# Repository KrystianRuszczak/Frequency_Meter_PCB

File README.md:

# STM32 Frequency Meter PCB

A custom frequency meter built around the STM32G431KBT6 microcontroller, combining an analog input stage, a four-layer PCB, and an OLED display in a compact embedded system.

## Repository Contents

KiCad project files, schematics and PCB layout.

## Project Status

The project is under development. Measurement range, accuracy, and input limits will be documented after hardware assembly and validation.

## Key components

| Component | Part / type | Role |
| --- | --- | --- |
| Microcontroller | STM32G431KBT6 | Frequency measurement, USB communication, and display control. |
| Input amplifier | LMH6629MF/NOPB | Amplifies the filtered RF input signal. |
| Comparator | TLV3601DBVR | Converts the amplified analog signal into clock pulses. |
| Frequency divider | SN74LVC1G80 | Divides the comparator output frequency by two before counting by the microcontroller. |
| Voltage reference | REF2033 | Provides the 1.65 V reference for analog biasing and the comparator threshold. |
| Voltage regulator | AP2112K-3.3 | Provides the regulated 3.3 V supply. |
| Crystal | ABM3B-16.000MHZ-10-1-U-T | Provides the external 16 MHz clock reference for the microcontroller. |
| USB-C connector | USB4105-GF-A | Provides power and USB connectivity. |
| USB ESD protection | USBLC6-2SC6 | Protects the USB data lines against electrostatic discharge. |
| RF input connector | 50 Ω SMA | Connects the measured signal to the RF input filter. |
| Display | I2C OLED module | Displays measurement results. |

This list covers the main components. Refer to the KiCad schematic for passive components, supporting circuitry, and exact part variants.

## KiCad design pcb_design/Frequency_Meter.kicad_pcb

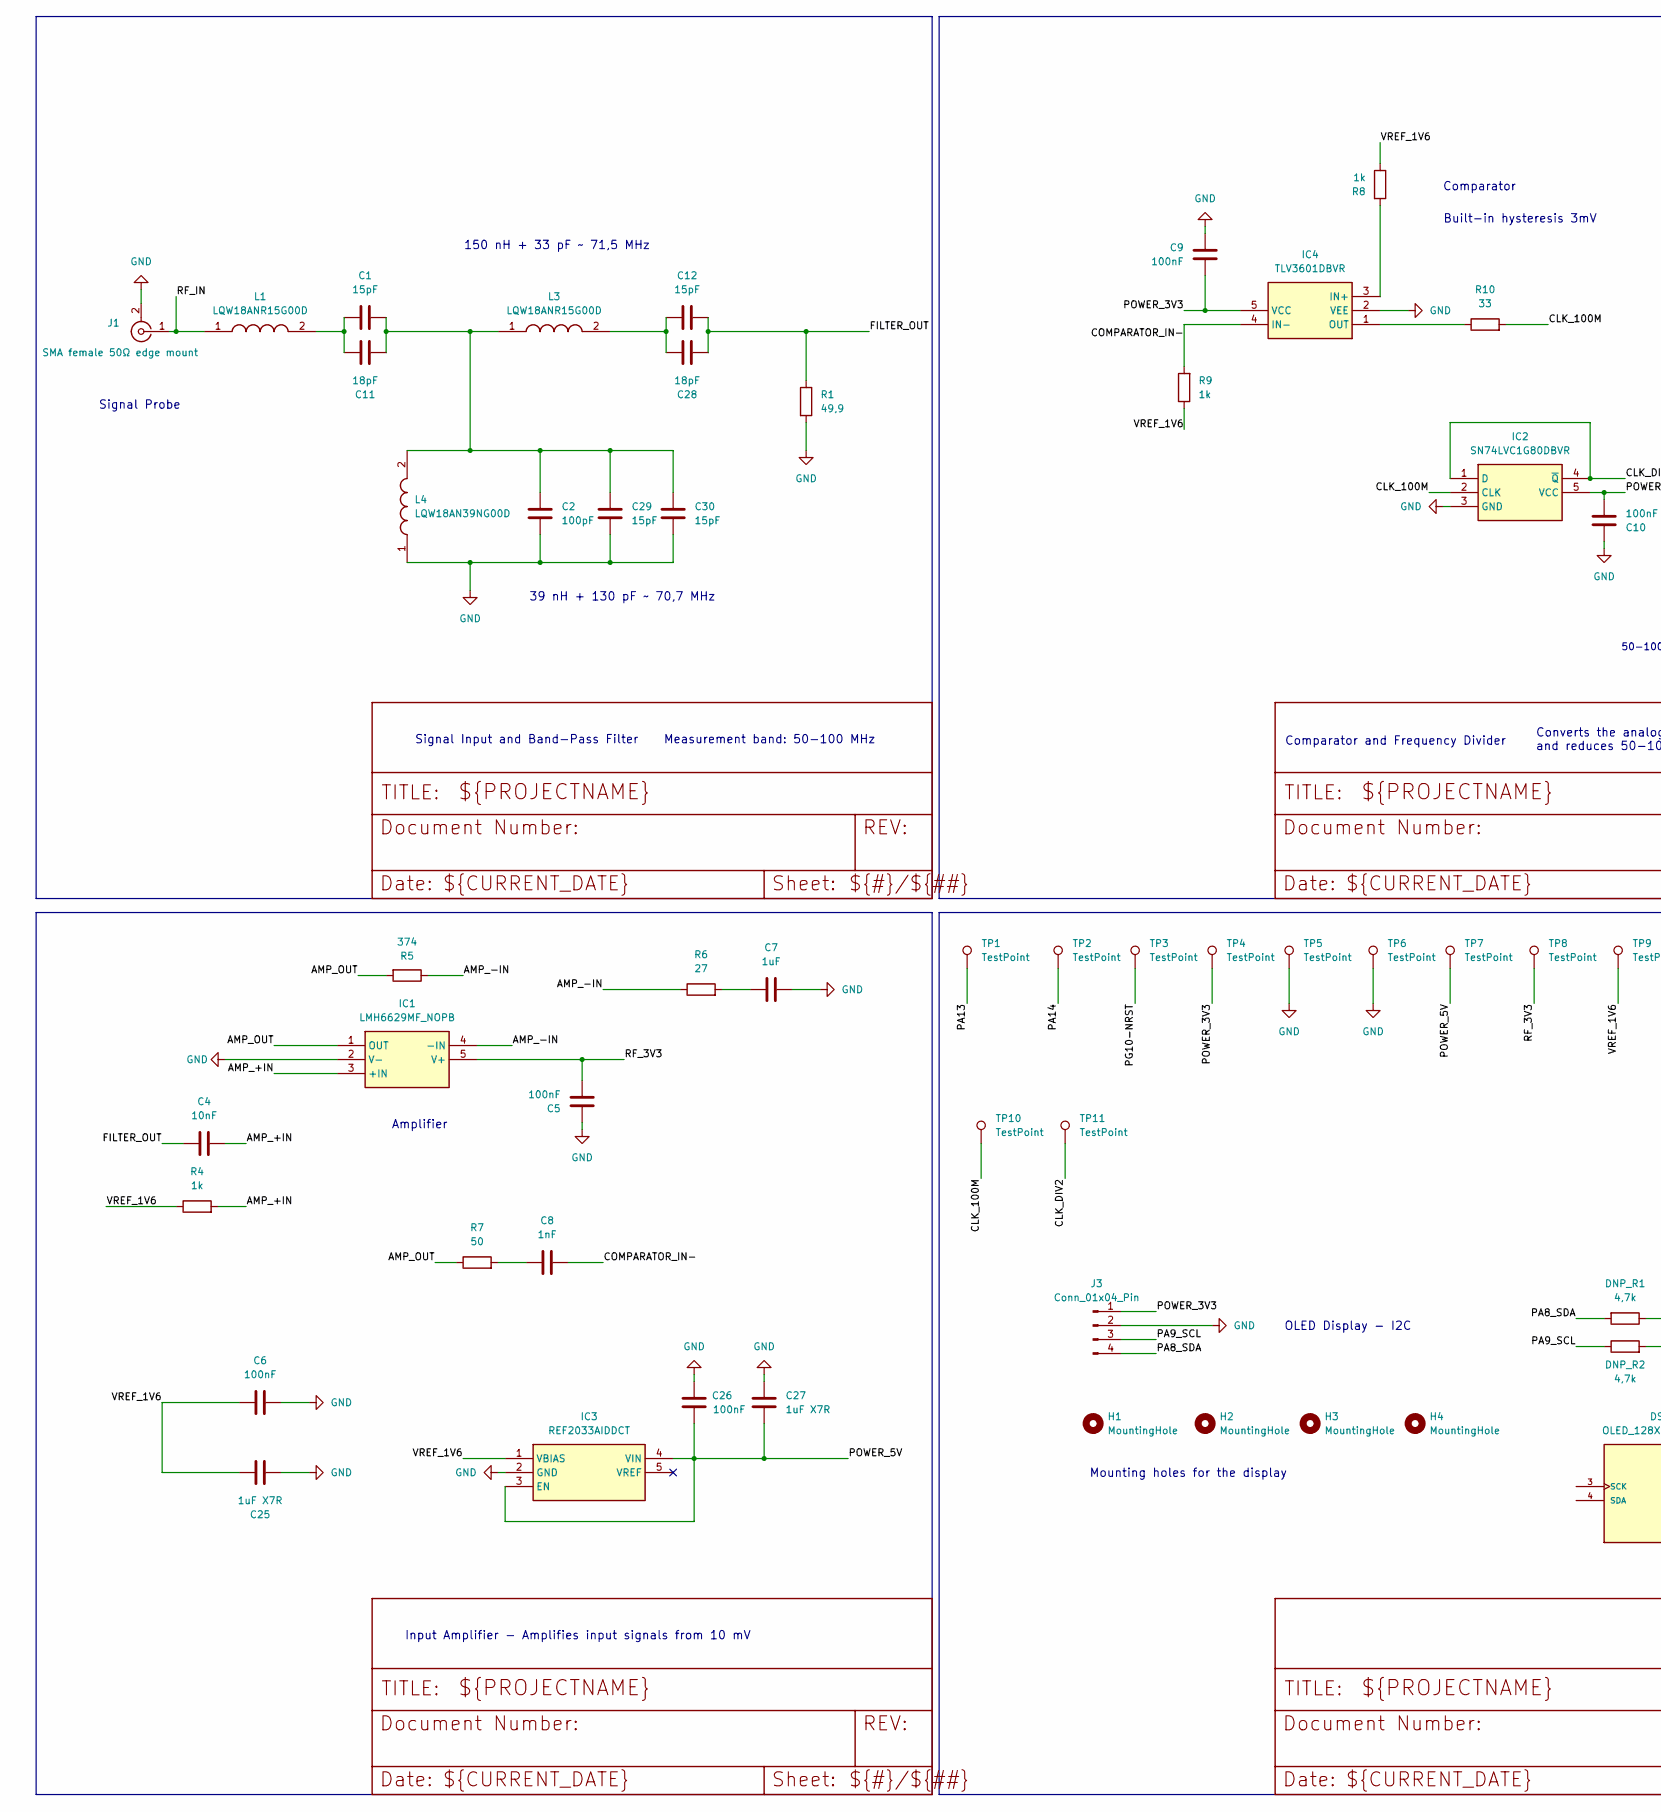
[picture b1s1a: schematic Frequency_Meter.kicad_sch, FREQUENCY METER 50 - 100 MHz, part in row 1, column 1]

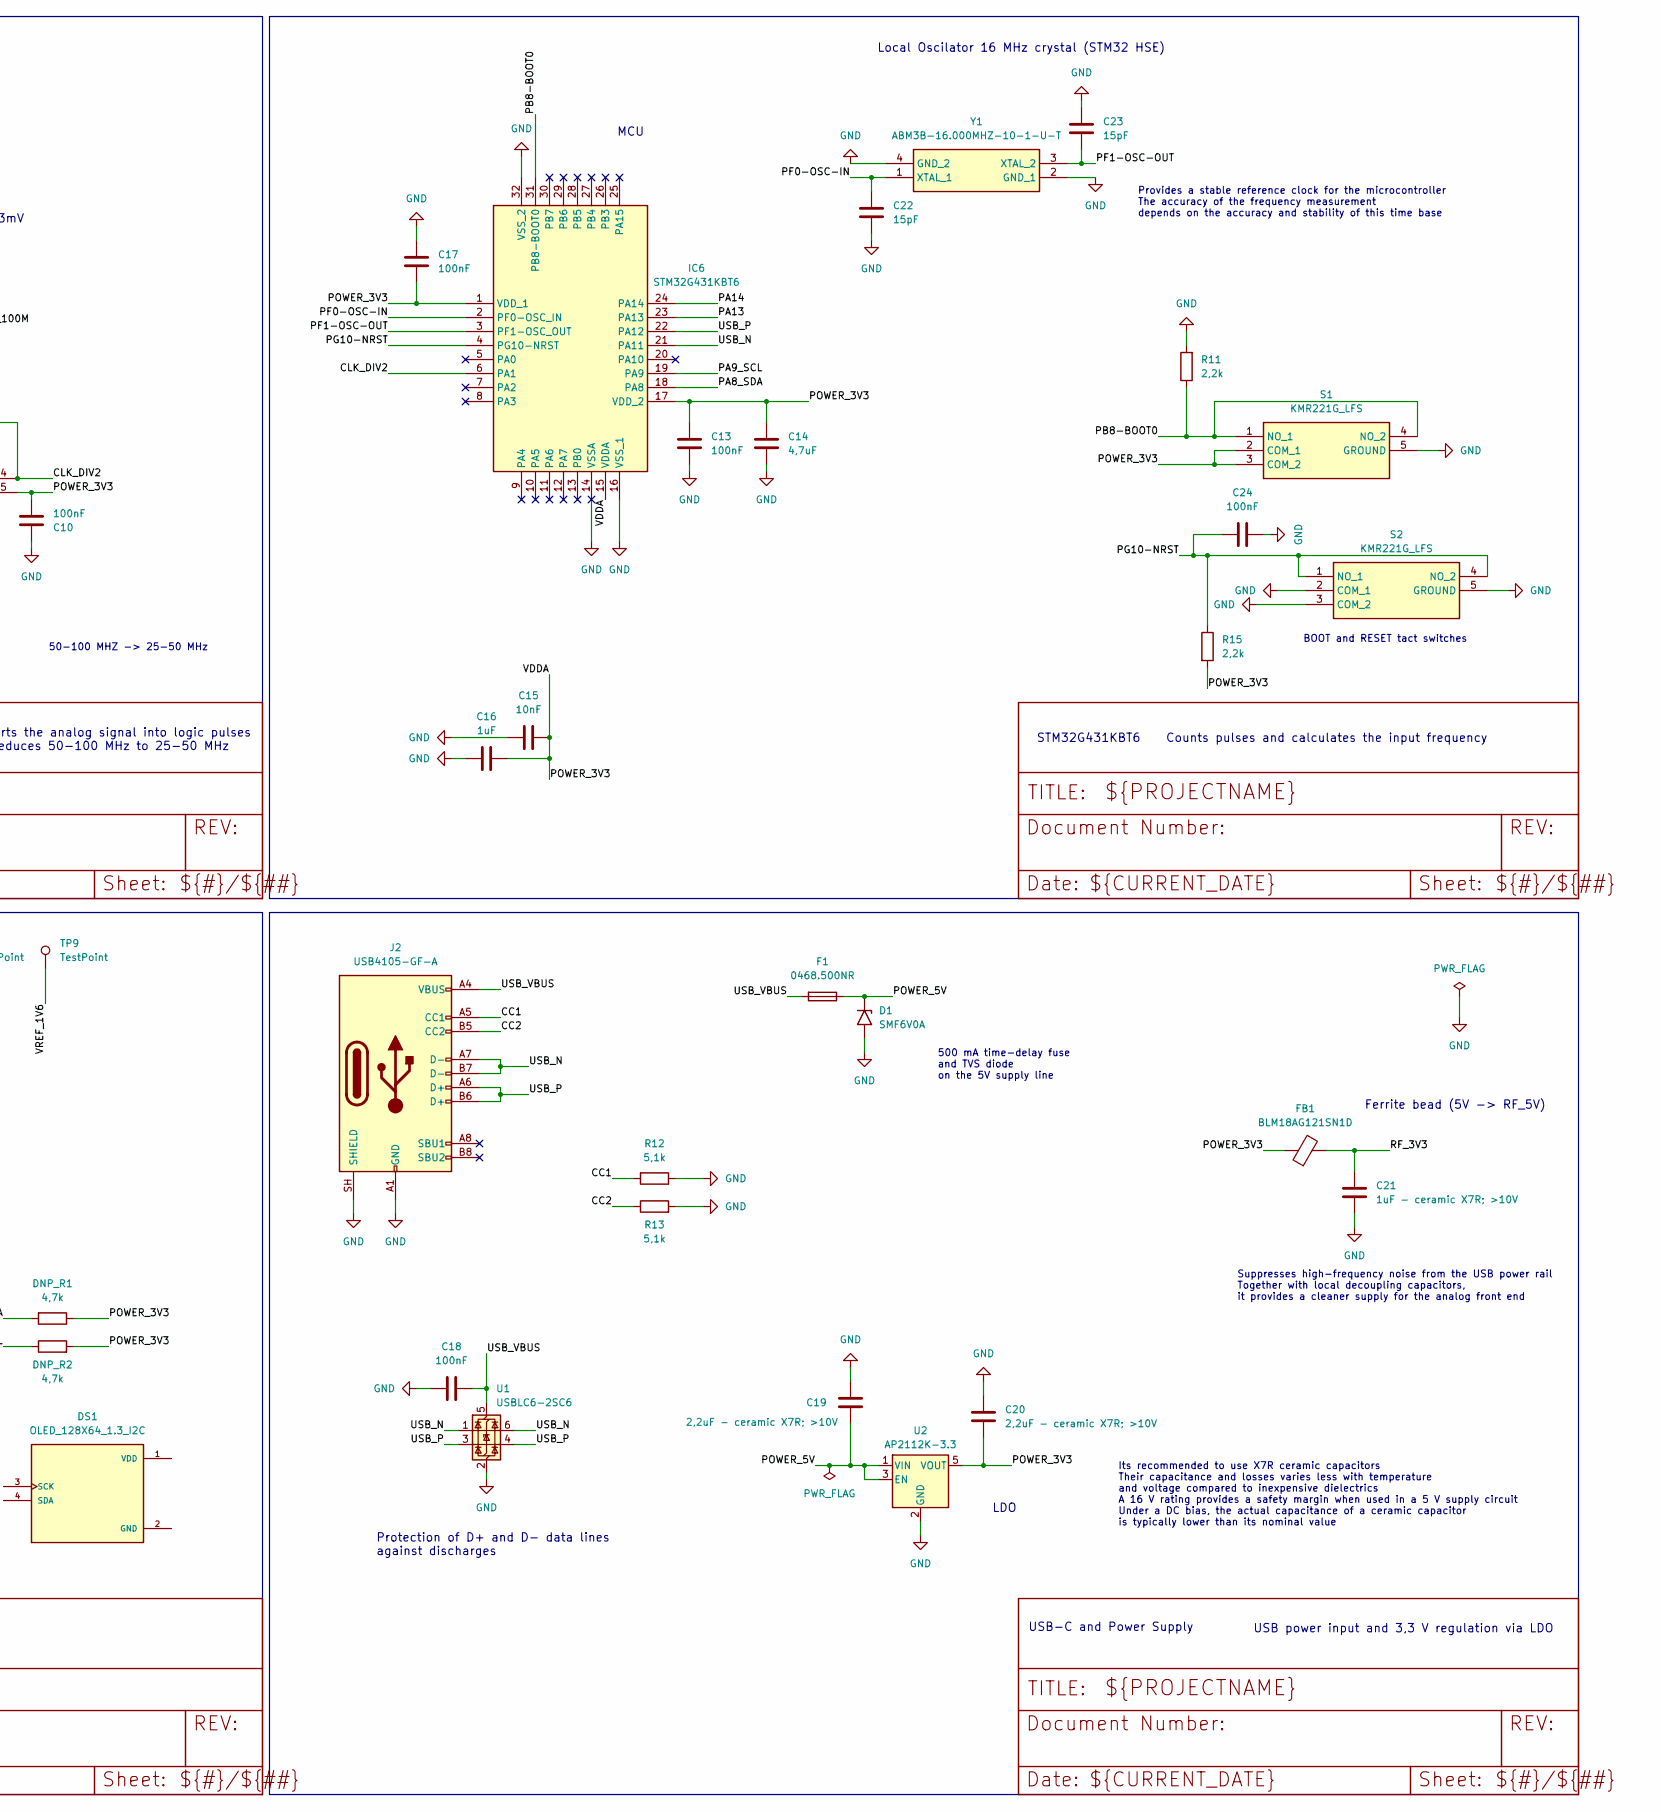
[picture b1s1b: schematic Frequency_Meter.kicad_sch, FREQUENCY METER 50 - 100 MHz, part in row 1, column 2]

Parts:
C1, C12, C22, C23, C29, C30: 15pF; C_0603_1608Metric
C2: 100pF; C_0603_1608Metric
C4, C15: 10nF; C_0805_2012Metric
C5, C6, C9, C10, C13, C17, C18, C24, C26: 100nF; C_0603_1608Metric
C7, C16: 1uF; C_0805_2012Metric
C8: 1nF; C_0603_1608Metric
C11, C28: 18pF; C_0603_1608Metric
C14: 4,7uF; C_0805_2012Metric
C19, C20: 2,2uF - ceramic X7R; >10V; C_0805_2012Metric
C21: 1uF - ceramic X7R; >10V; C_0805_2012Metric
C25, C27: 1uF X7R; C_0805_2012Metric
D1: SMF6V0A; D_SMF
DNP_R1, DNP_R2: 4,7k; R_0603_1608Metric
DS1: OLED_128X64_1.3_I2C; LCD_OLED_128X64_1.3_I2C; PARTREV NA
F1: 0468.500NR; Fuse_1206_3216Metric
FB1: BLM18AG121SN1D; L_0603_1608Metric
H1, H2, H3, H4: MountingHole; MountingHole_2.2mm_M2
IC1: LMH6629MF_NOPB; SOT95P280X145-5N; Mouser Part Number 926-LMH6629MF/NOPB
IC2: SN74LVC1G80DBVR; SOT95P280X145-5N; Mouser Part Number 595-SN74LVC1G80DBVR
IC3: REF2033AIDDCT; SOT95P280X110-5N; Mouser Part Number 595-REF2033AIDDCT
IC4: TLV3601DBVR; SOT95P280X145-5N; Mouser Part Number 595-TLV3601DBVR
IC6: STM32G431KBT6; QFP80P900X900X160-32N; Manufacturer_Part_Number STM32G431KBT6
J1: SMA female 50Ω edge mount; SMA_Amphenol_132289_EdgeMount
J2: USB4105-GF-A; USB_C_Receptacle_GCT_USB4105-xx-A_16P_TopMnt_Horizontal
J3: Conn_01x04_Pin; PinSocket_1x04_P2.54mm_Vertical
L1, L3: LQW18ANR15G00D; L_0603_1608Metric; Manufacturer_Part_Number LQW18ANR15G00D
L4: LQW18AN39NG00D; L_0603_1608Metric; Manufacturer_Part_Number LQW18AN39NG00D
R1: 49,9; R_0603_1608Metric
R4, R8, R9: 1k; R_0603_1608Metric
R5: 374; R_0603_1608Metric
R6: 27; R_0603_1608Metric
R7: 50; R_0603_1608Metric
R10: 33; R_0603_1608Metric
R11, R15: 2,2k; R_0603_1608Metric
R12, R13: 5,1k; R_0603_1608Metric
S1, S2: KMR221G_LFS; KMR221GLFS; Manufacturer_Part_Number KMR221G LFS
TP1, TP2, TP3, TP4, TP5, TP6, TP7, TP8, TP9, TP10, TP11: TestPoint; TestPoint_Pad_D1.0mm
U1: USBLC6-2SC6; SOT-23-6
U2: AP2112K-3.3; SOT-23-5
Y1: ABM3B-16.000MHZ-10-1-U-T; ABM3B; Manufacturer_Part_Number ABM3B-16.000MHZ-10-1-U-T

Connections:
/AMP_+IN: C4.2, IC1.3 (+IN), R4.2
/AMP_-IN: IC1.4 (-IN), R5.1, R6.1
/AMP_OUT: IC1.1 (OUT), R5.2, R7.1
/CC1: J2.A5 (CC1), R12.2
/CC2: J2.B5 (CC2), R13.1
/CLK_100M: IC2.2 (CLK), R10.2, TP10.1 (1_1)
/CLK_DIV2: IC2.1 (D), IC2.4 (~Q), IC6.6 (PA1), TP11.1 (1_1)
/COMPARATOR_IN-: C8.1, IC4.4 (IN-), R9.2
/FILTER_OUT: C4.1, C12.2, C28.2, R1.1
/PA8_SDA: DNP_R1.2, IC6.18 (PA8), J3.4
/PA9_SCL: DNP_R2.1, IC6.19 (PA9), J3.3
/PA13: IC6.23 (PA13), TP1.1 (1_1)
/PA14: IC6.24 (PA14), TP2.1 (1_1)
/PB8-BOOT0: IC6.31 (PB8-BOOT0), R11.1, S1.1 (NO_1), S1.4 (NO_2)
/PF0-OSC-IN: C22.1, IC6.2 (PF0-OSC_IN), Y1.1 (XTAL_1)
/PF1-OSC-OUT: C23.2, IC6.3 (PF1-OSC_OUT), Y1.3 (XTAL_2)
/PG10-NRST: C24.1, IC6.4 (PG10-NRST), R15.1, S2.1 (NO_1), S2.4 (NO_2), TP3.1 (1_1)
/POWER_3V3: C9.1, C10.2, C13.1, C14.1, C15.2, C16.2, C17.1, C20.2, DNP_R1.1, DNP_R2.2, FB1.1, IC2.5 (VCC), IC4.5 (VCC), IC6.1 (VDD_1), IC6.15 (VDDA), IC6.17 (VDD_2), J3.1, R15.2, S1.2 (COM_1), S1.3 (COM_2), TP4.1 (1_1), U2.5 (VOUT)
/POWER_5V: C19.2, C26.1, C27.2, D1.1 (A1), F1.1, IC3.3 (EN), IC3.4 (VIN), TP7.1 (1_1), U2.1 (VIN), U2.3 (EN)
/RF_3V3: C5.2, C21.1, FB1.2, IC1.5 (V+), TP8.1 (1_1)
/RF_IN: J1.1 (In), L1.1
/USB_N: IC6.21 (PA11), J2.A7 (D-), J2.B7 (D-), U1.1 (I/O1), U1.6 (I/O1)
/USB_P: IC6.22 (PA12), J2.A6 (D+), J2.B6 (D+), U1.3 (I/O2), U1.4 (I/O2)
/USB_VBUS: C18.2, F1.2, J2.A4 (VBUS), J2.A9 (VBUS), J2.B4 (VBUS), J2.B9 (VBUS), U1.5 (VBUS)
/VREF_1V6: C6.1, C25.1, IC3.1 (VBIAS), R4.1, R8.1, R9.1, TP9.1 (1_1)
GND: C2.2, C5.1, C6.2, C7.2, C9.2, C10.1, C13.2, C14.2, C15.1, C16.1, C17.2, C18.1, C19.1, C20.1, C21.2, C22.2, C23.1, C24.2, C25.2, C26.2, C27.1, C29.1, C30.1, D1.2 (A2), IC1.2 (V-), IC2.3 (GND), IC3.2 (GND), IC4.2 (VEE), IC6.14 (VSSA), IC6.16 (VSS_1), IC6.32 (VSS_2), J1.2 (Ext), J2.A1 (GND), J2.A12 (GND), J2.B1 (GND), J2.B12 (GND), J2.SH (SHIELD), J3.2, L4.1, R1.2, R11.2, R12.1, R13.2, S1.5 (GROUND), S2.2 (COM_1), S2.3 (COM_2), S2.5 (GROUND), TP5.1 (1_1), TP6.1 (1_1), U1.2 (GND), U2.2 (GND), Y1.2 (GND_1), Y1.4 (GND_2)
unnamed: C1.1, C11.1, L1.2
unnamed: C1.2, C2.1, C11.2, C29.2, C30.2, L3.1, L4.2
unnamed: C7.1, R6.2
unnamed: C8.2, R7.2
unnamed: C12.1, C28.1, L3.2
unnamed: IC4.3 (IN+), R8.2
unnamed: IC4.1 (OUT), R10.1

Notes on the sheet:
Input Amplifier - Amplifies input signals from 10 mV
STM32G431KBT6 Counts pulses and calculates the input frequency
Provides a stable reference clock for the microcontroller The accuracy of the frequency measurement depends on the accuracy and stability of this time base
MCU
BOOT and RESET tact switches
Converts the analog signal into logic pulses and reduces 50-100 MHz to 25-50 MHz
LDO
Protection of D+ and D− data lines against discharges
150 nH + 33 pF ~ 71,5 MHz
Its recommended to use X7R ceramic capacitors Their capacitance and losses varies less with temperature and voltage compared to inexpensive dielectrics A 16 V rating provides a safety margin when used in a 5 V supply circuit Under a DC bias, the actual capacitance of a ceramic capacitor is typicall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
Mounting holes for the display
Comparator and Frequency Divider
500 mA time-delay fuse and TVS diode on the 5V supply line
Amplifier
Signal Input and Band-Pass Filter Measurement band: 50-100 MHz
50-100 MHZ -> 25-50 MHz
USB-C and Power Supply
Signal Probe
Suppresses high-frequency noise from the USB power rail Together with local decoupling capacitors, it provides a cleaner supply for the analog front end
Comparator
39 nH + 130 pF ~ 70,7 MHz
Ferrite bead (5V -> RF_5V)
Built-in hysteresis 3mV
OLED Display - I2C
USB power input and 3,3 V regulation via LDO
Local Oscilator 16 MHz crystal (STM32 HSE)

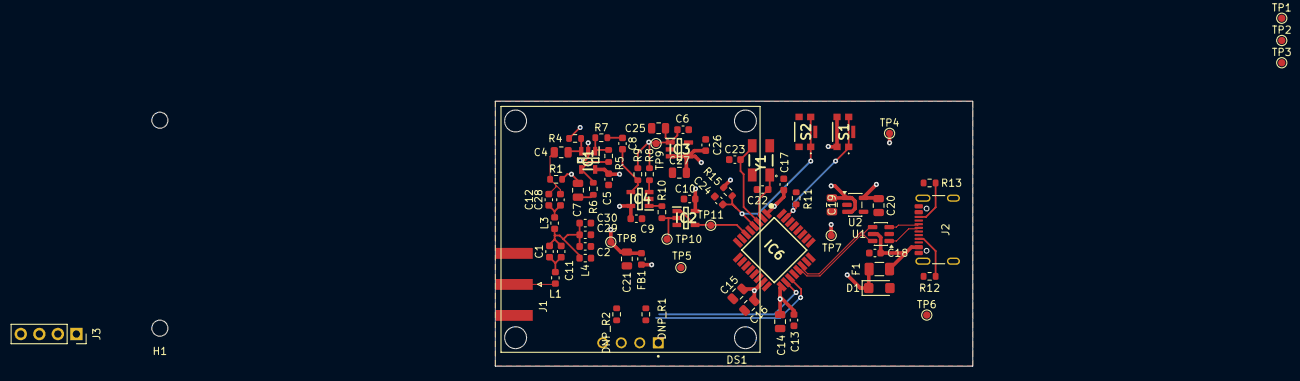
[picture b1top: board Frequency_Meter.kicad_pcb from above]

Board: 4 copper layers, 65.4 x 36.3 mm, 78 parts (0 on the bottom side), 33 nets.
